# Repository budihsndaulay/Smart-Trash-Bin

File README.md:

# Smart-Trash-Bin
For Education In High School

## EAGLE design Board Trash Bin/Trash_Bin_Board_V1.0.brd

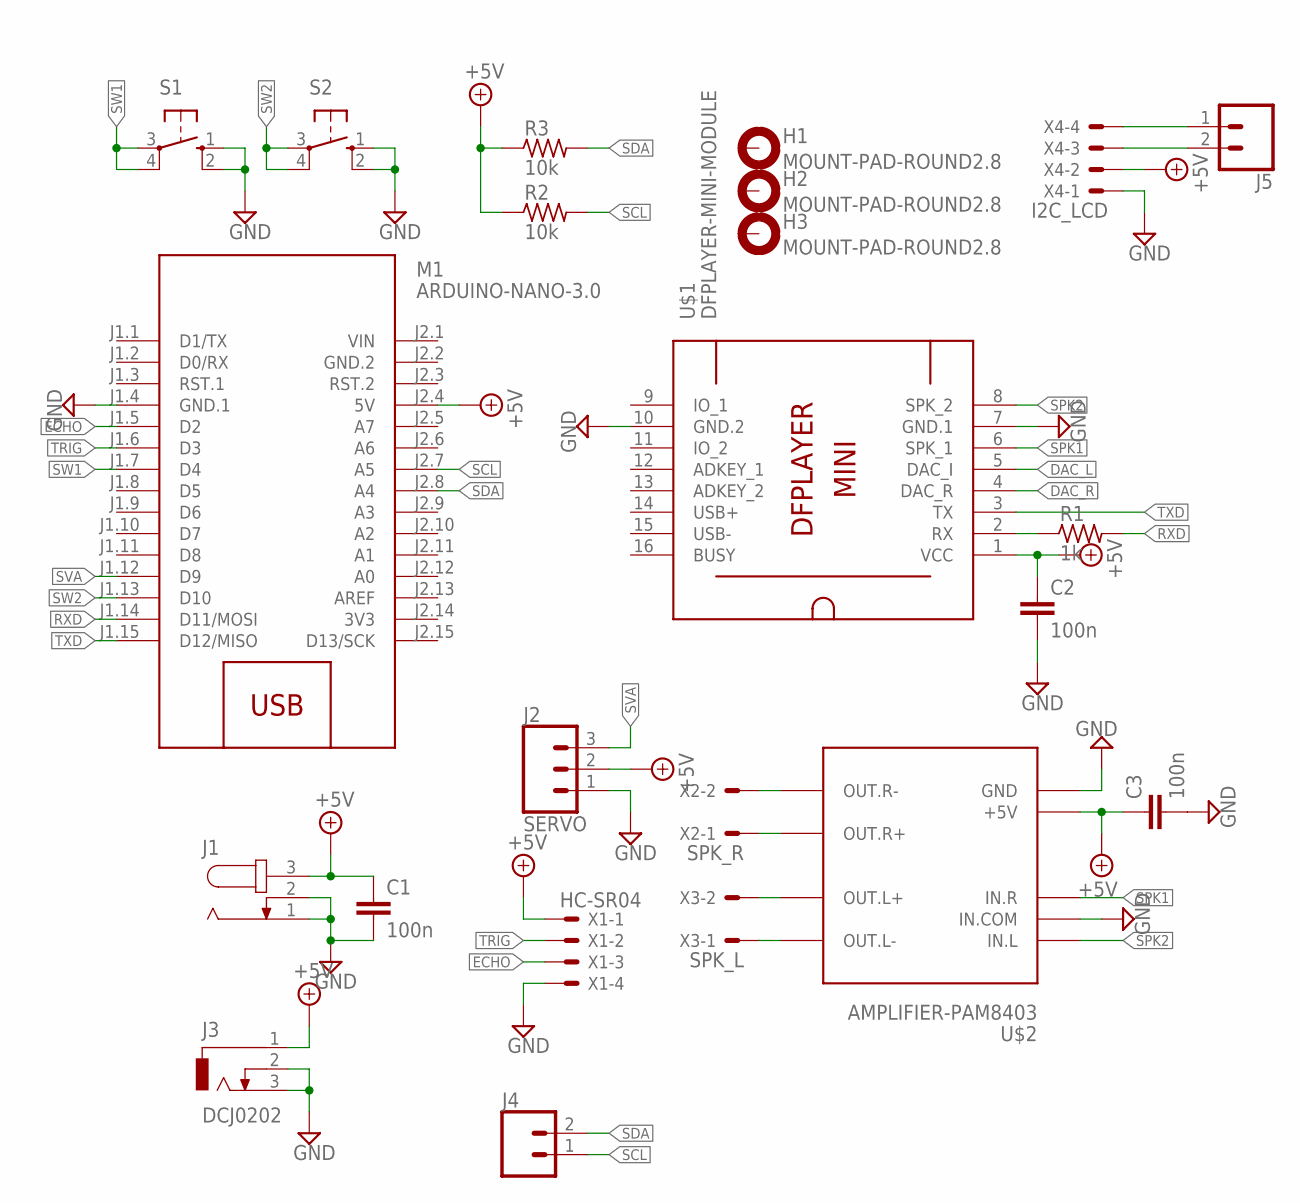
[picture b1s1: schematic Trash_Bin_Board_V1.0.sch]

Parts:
C1, C2, C3: 100n; C2.5-3
H1, H2, H3: MOUNT-PAD-ROUND2.8; 2,8-PAD
J1: JACK-PLUG0; SPC4077
J2: SERVO; 1X03
J3: DCJ0202
J4, J5: CONN_02; 1X02
M1: ARDUINO-NANO-3.0
R1: 1k; 0207/7
R2, R3: 10k; 0207/7
S1, S2: 10-XX; B3F-10XX
U$1: DFPLAYER-MINI-MODULE
U$2: AMPLIFIER-PAM8403
X1: HC-SR04; JST-XH-04-PACKAGE-LONG-PAD
X2: SPK_R; JST-XH-02-PACKAGE-LONG-PAD
X3: SPK_L; JST-XH-02-PACKAGE-LONG-PAD
X4: I2C_LCD; JST-XH-04-PACKAGE-LONG-PAD

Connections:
3V3: M1.J2.14 (3V3)
+5V: C1.1, C2.1, C3.1, J1.3, J2.2, J3.1, M1.J2.4 (5V), R2.1, R3.1, U$1.1 (VCC), U$2.+5V, X1.1, X4.2
DAC_L: U$1.5 (DAC_I)
DAC_R: U$1.4 (DAC_R)
ECHO: M1.J1.5 (D2), X1.3
GND: C1.2, C2.2, C3.2, J1.1, J1.2, J2.1, J3.2, J3.3, M1.J1.4 (GND.1), S1.1 (S), S1.2 (S1), S2.1 (S), S2.2 (S1), U$1.7 (GND.1), U$1.10 (GND.2), U$2.GND, U$2.IN.COM, X1.4, X4.1
GND.2: M1.J2.2 (GND.2)
unnamed: R1.1, U$1.2 (RX)
unnamed: U$2.OUT.R-, X2.2
unnamed: U$2.OUT.R+, X2.1
unnamed: U$2.OUT.L+, X3.2
unnamed: U$2.OUT.L-, X3.1
unnamed: J5.1, X4.4
unnamed: J5.2, X4.3
RXD: M1.J1.14 (D11/MOSI), R1.2
SCL: J4.1, M1.J2.7 (A5), R2.2
SDA: J4.2, M1.J2.8 (A4), R3.2
SPK1: U$1.6 (SPK_1), U$2.IN.R
SPK2: U$1.8 (SPK_2), U$2.IN.L
SVA: J2.3, M1.J1.12 (D9)
SW1: M1.J1.7 (D4), S1.3, S1.4 (P1)
SW2: M1.J1.13 (D10), S2.3, S2.4 (P1)
TRIG: M1.J1.6 (D3), X1.2
TXD: M1.J1.15 (D12/MISO), U$1.3 (TX)
VIN: M1.J2.1 (VIN)

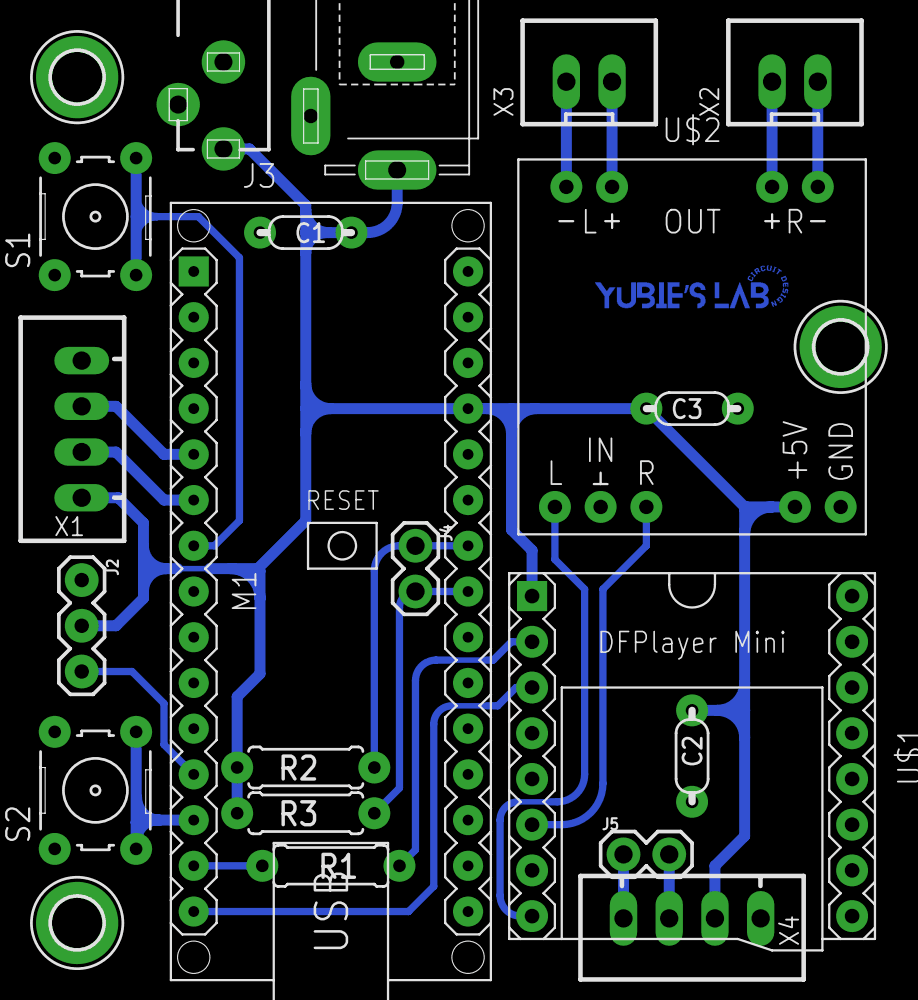
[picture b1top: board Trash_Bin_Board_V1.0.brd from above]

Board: 2 copper layers, 23 parts (0 on the bottom side), 20 nets.

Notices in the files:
parts and their libraries:
diy-modules_lcd: Released under the Creative Commons Attribution 4.0 International License: http://creativecommons.org/licenses/by/4.0
SparkFun-Connectors: Licensing: Creative Commons ShareAlike 4.0 International - https://creativecommons.org/licenses/by-sa/4.0
